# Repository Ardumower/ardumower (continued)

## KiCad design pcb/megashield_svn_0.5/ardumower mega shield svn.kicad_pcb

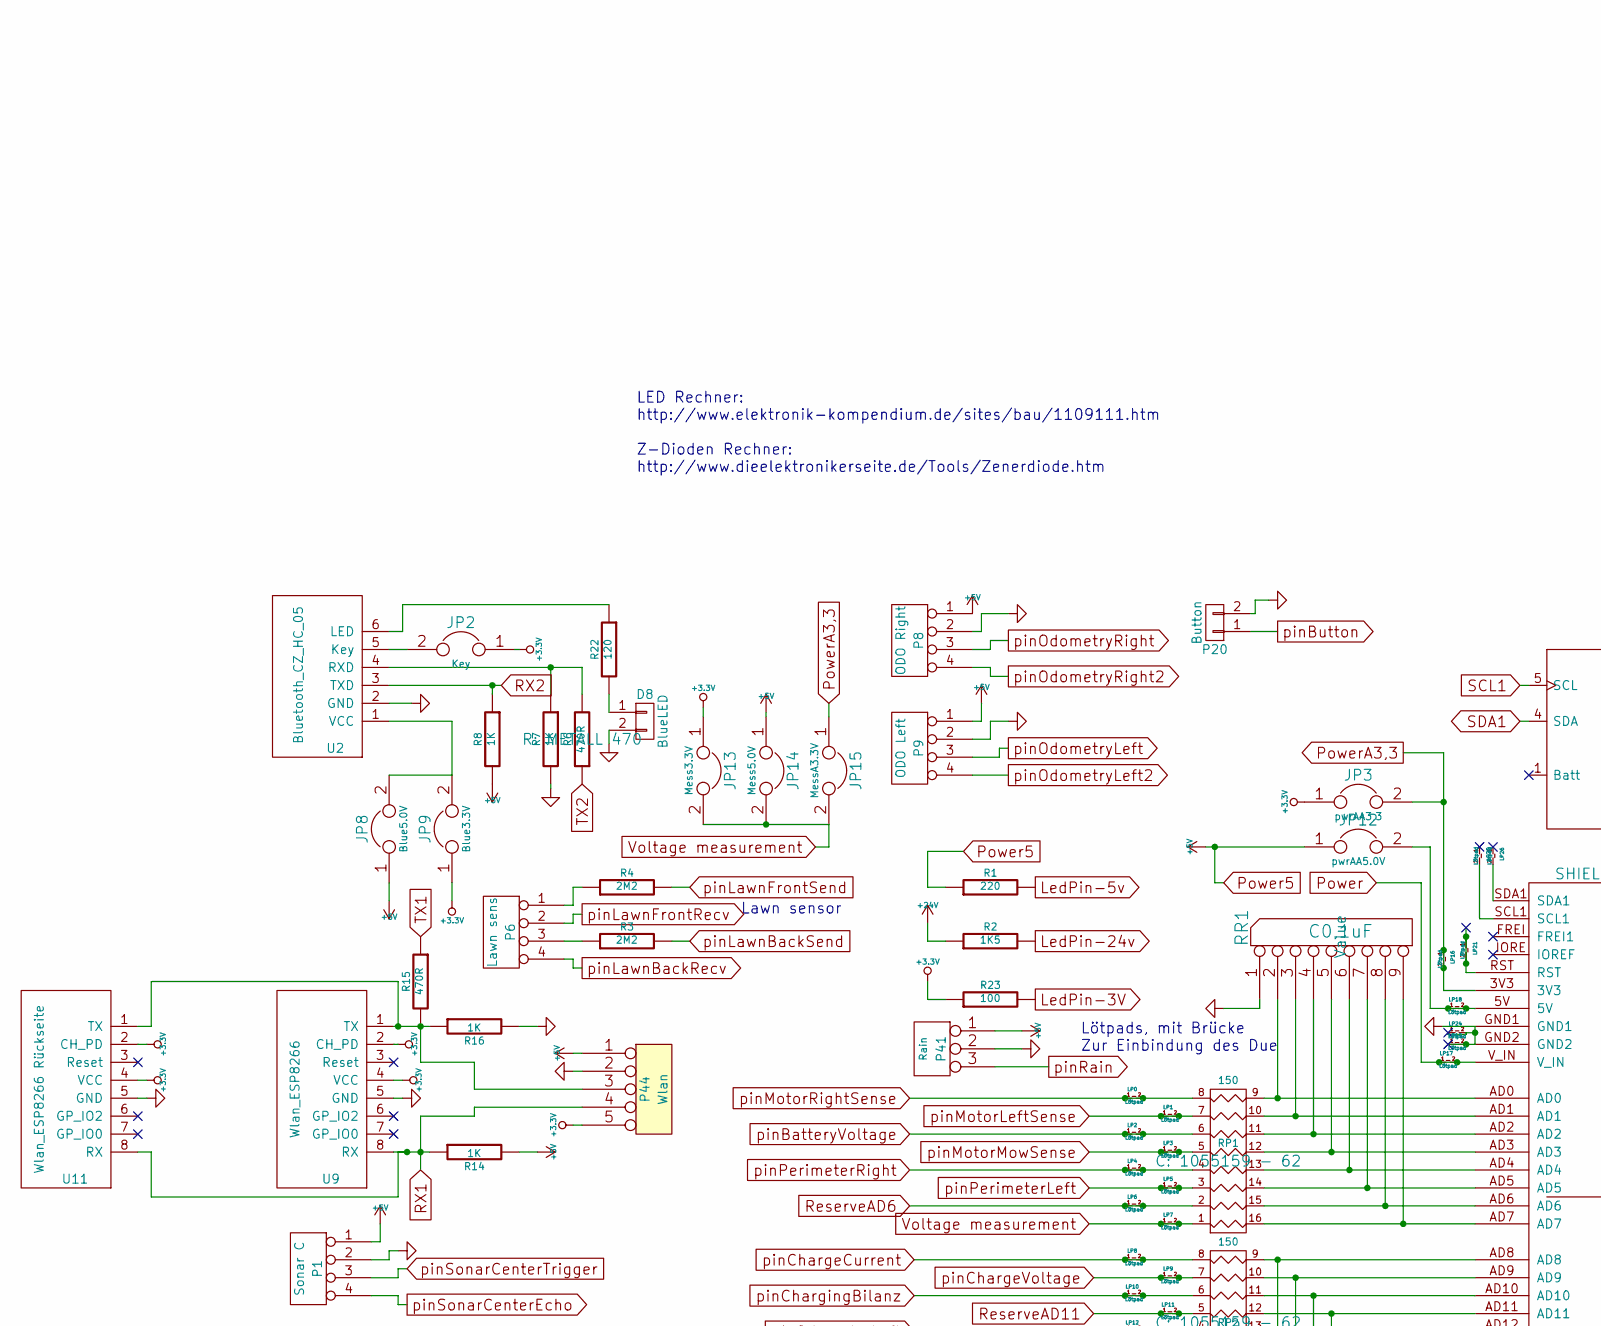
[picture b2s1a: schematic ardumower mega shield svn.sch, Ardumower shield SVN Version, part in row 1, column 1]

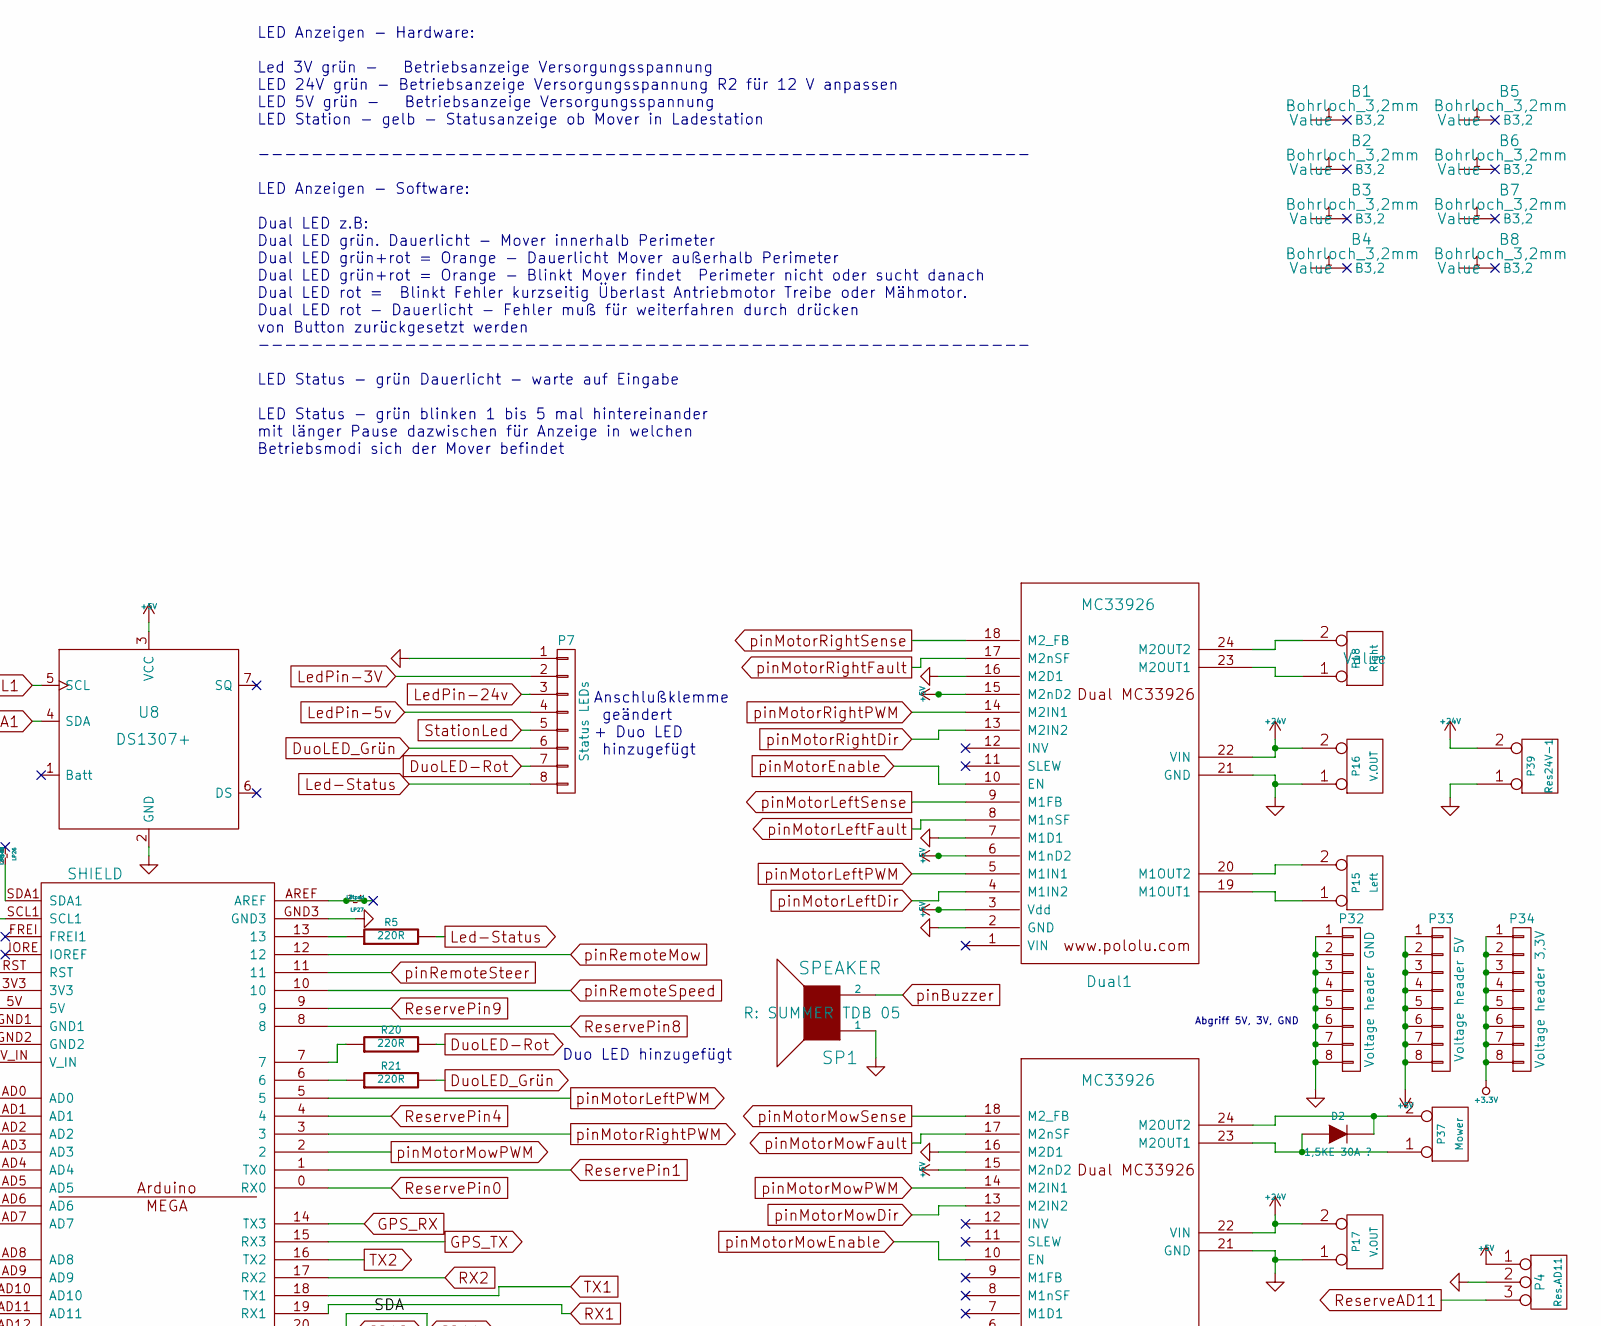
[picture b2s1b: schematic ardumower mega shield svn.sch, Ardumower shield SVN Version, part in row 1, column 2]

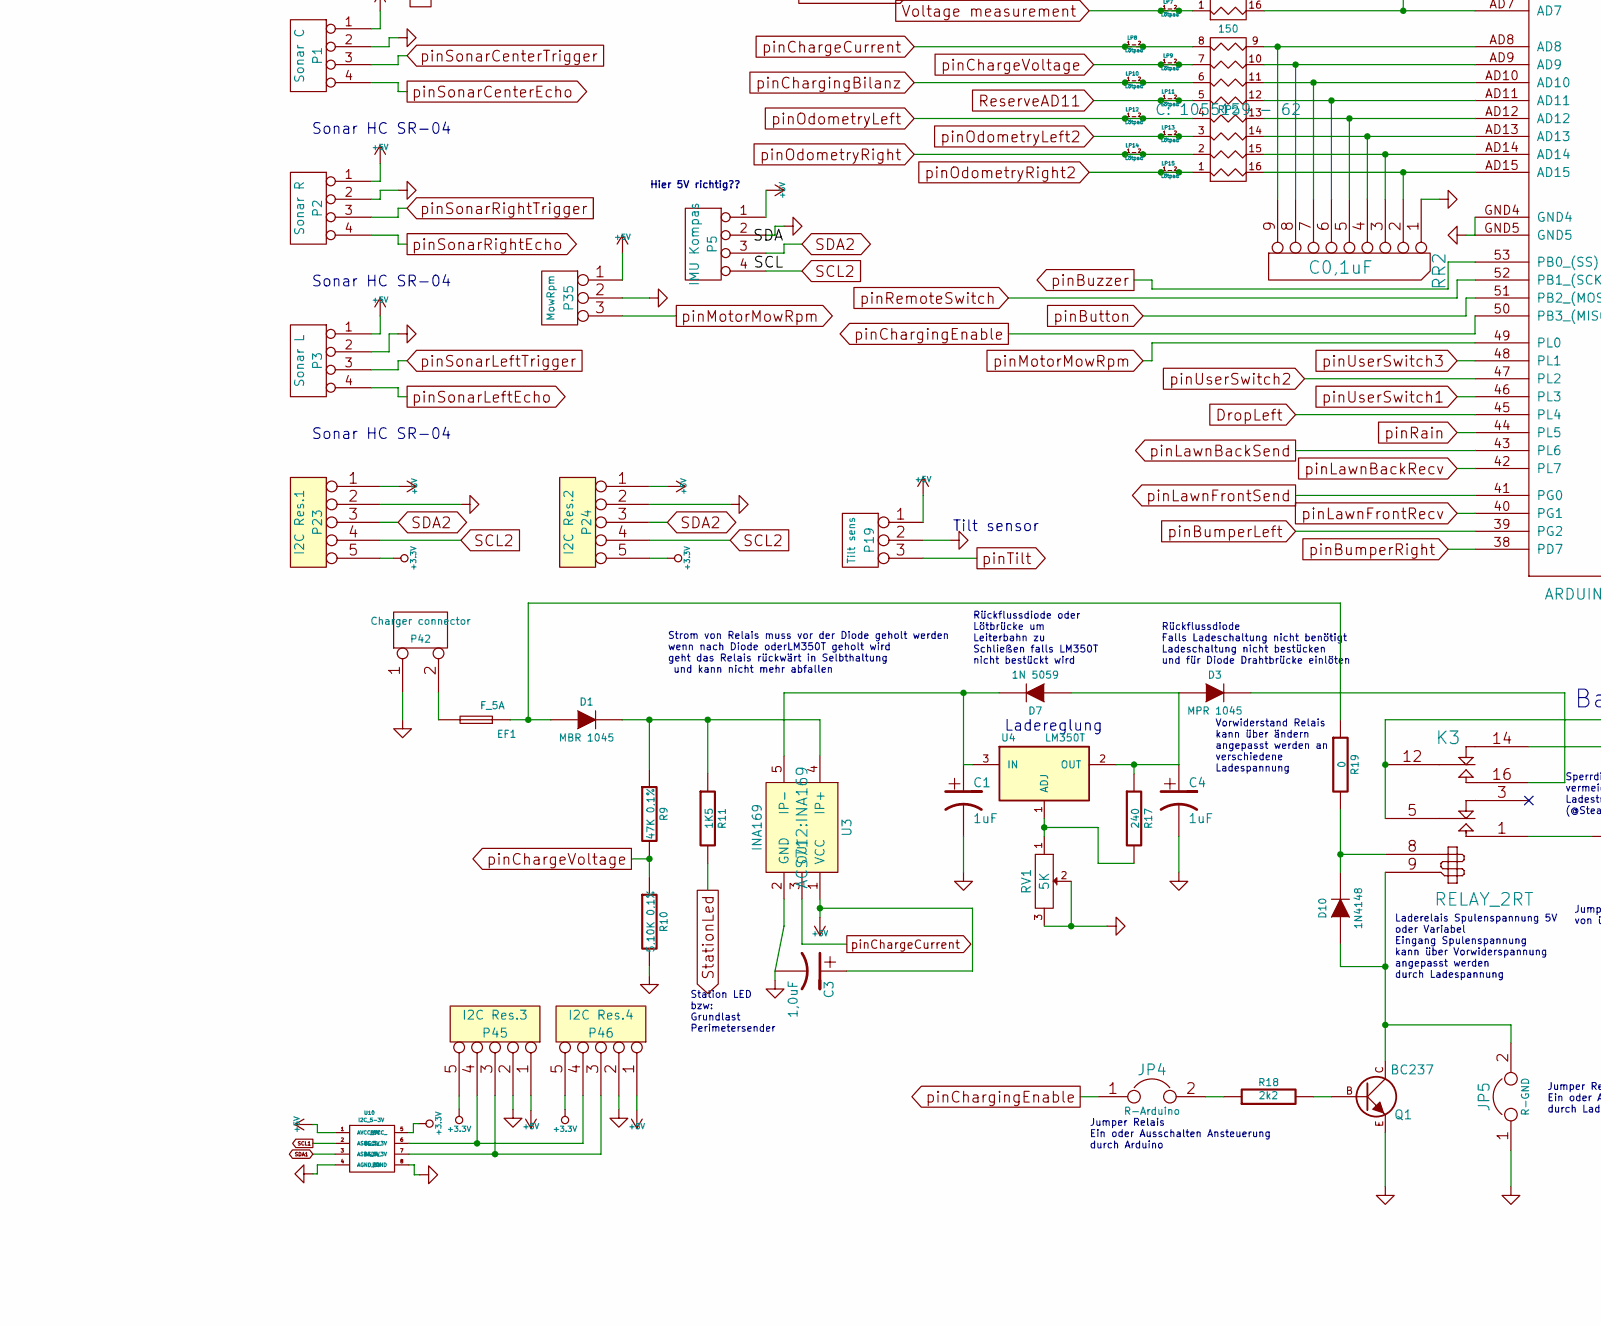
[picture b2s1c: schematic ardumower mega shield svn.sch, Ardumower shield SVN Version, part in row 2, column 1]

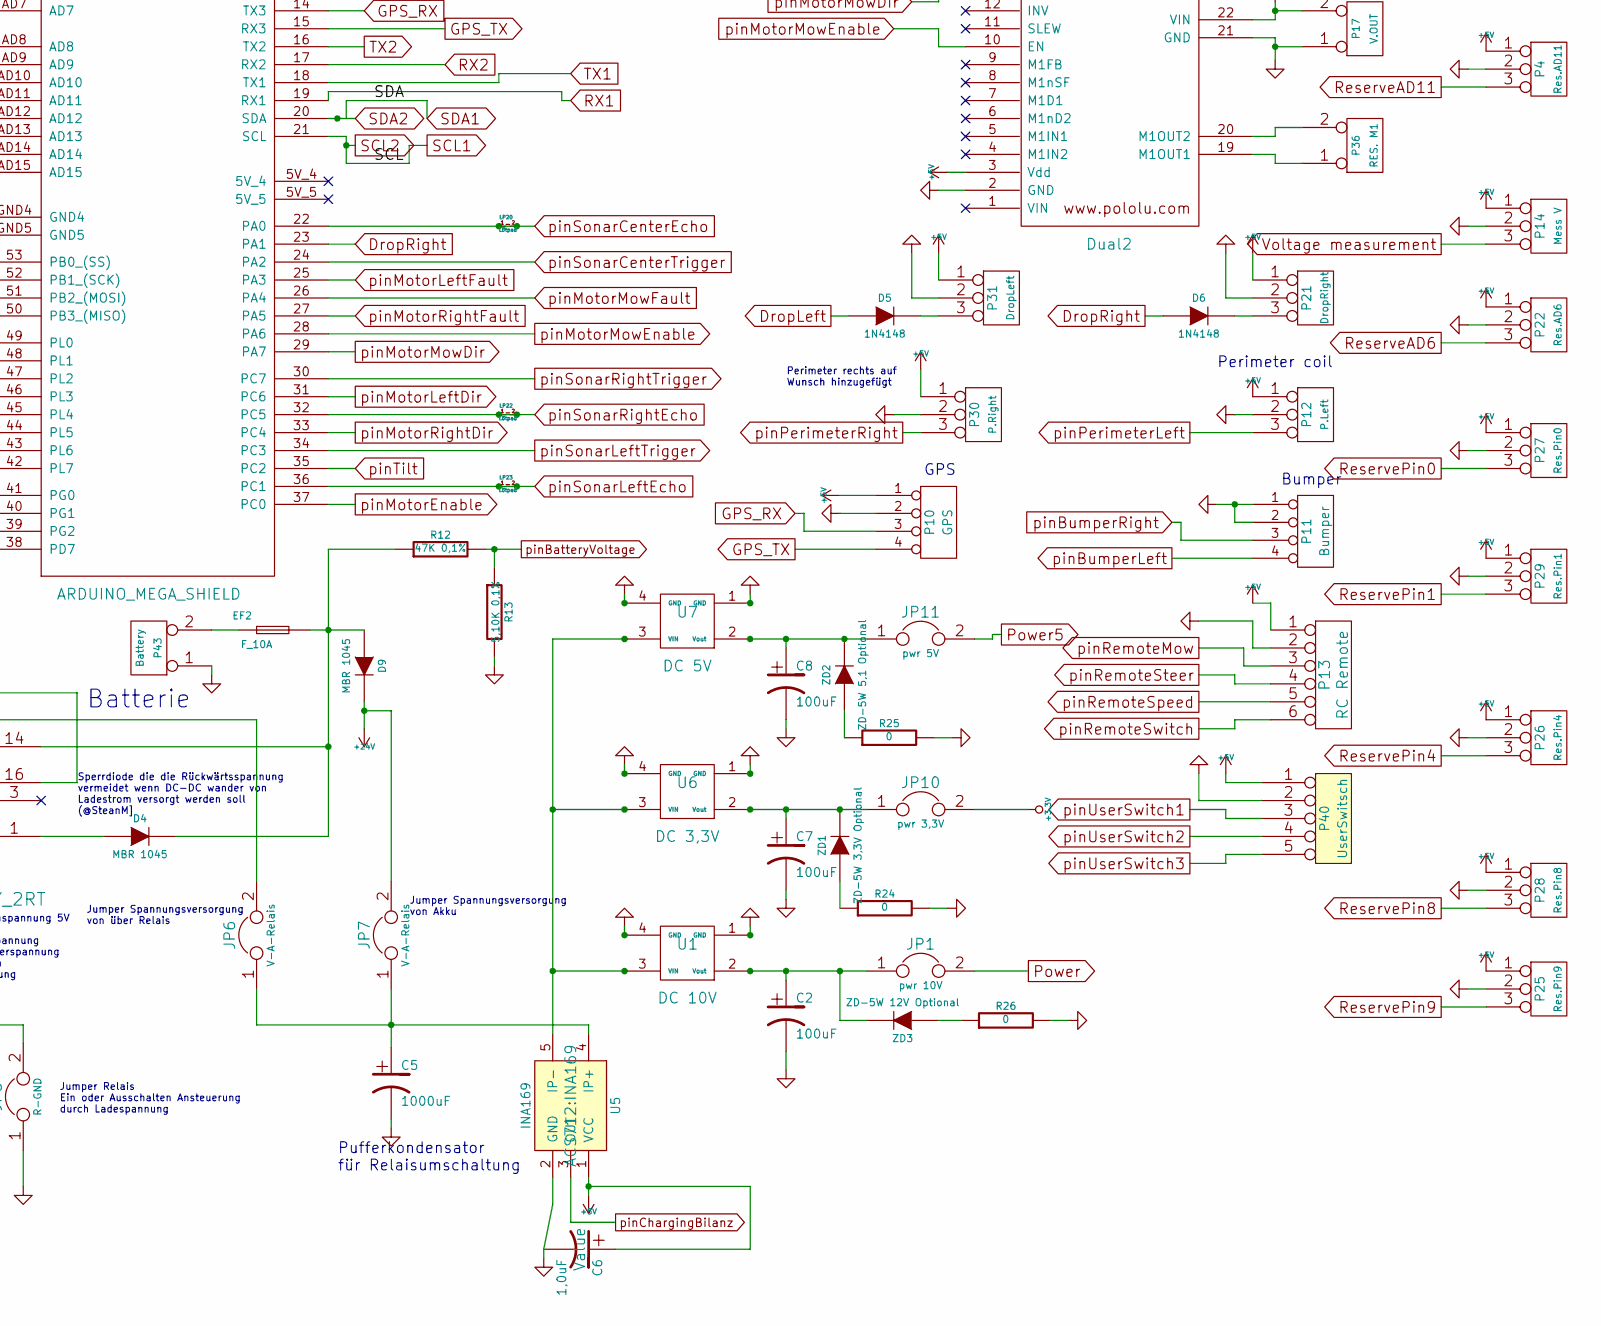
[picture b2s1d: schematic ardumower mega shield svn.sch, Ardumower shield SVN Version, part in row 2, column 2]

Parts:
B1, B2, B3, B4, B5, B6, B7, B8: Bohrloch_3,2mm
C1, C4: 1uF; Elko_vert_11.2x6.3mm_RM2.5_RM5.0
C2, C7, C8: 100uF; Elko_vert_11.2x6.3mm_RM2.5_RM5.0
C3, C6: 1,0uF; Elko_vert_11.2x6.3mm_RM2.5_RM5.0
C5: 1000uF; Elko_vert_31.5x16mm_RM7.5
D1, D4: MBR 1045; MBR1045
D2: 1,5KE 30A ?; Diode_ligend_RM10
D3: MPR 1045; MBR1045
D5, D6, D10: 1N4148; Diode_ligend_RM10
D7: 1N 5059; Diode_ligend_RM10
D8: BlueLED; Diode_LED_5mm_round_vertical
D9: MBR 1045; MBR1045_liegend
Dual1, Dual2: MC33926; MC_33926_31polig_mit_Bohrloch_neue_Masse
EF1: F_5A; Fuseholder_Reichelt_PL112000
EF2: F_10A; Fuseholder_Reichelt_PL112000
JP1: pwr 10V; Pin_Header_Straight_1x02
JP2: Key; Pin_Header_Straight_1x02
JP3: pwrAA3,3; Pin_Header_Straight_1x02
JP4: R-Arduino; Pin_Header_Straight_1x02
JP5: R-GND; Pin_Header_Straight_1x02
JP6, JP7: V-A-Relais; Pin_Header_Straight_1x02
JP8: Blue5.0V; Pin_Header_Straight_1x02
JP9: Blue3.3V; Pin_Header_Straight_1x02
JP10: pwr 3,3V; Pin_Header_Straight_1x02
JP11: pwr 5V; Pin_Header_Straight_1x02
JP12: pwrAA5.0V; Pin_Header_Straight_1x02
JP13: Mess3.3V; Pin_Header_Straight_1x02
JP14: Mess5.0V; Pin_Header_Straight_1x02
JP15: MessA3.3V; Pin_Header_Straight_1x02
K3: RELAY_2RT; Relais_DPDT_Schrack-RT2_RM5mm_3D_Kontaktbelegung_geändert_F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
LP0, LP1, LP2, LP3, LP4, LP5, LP6, LP7, LP8, LP9, LP10, LP11, LP12, LP13, LP14, LP15, LP16, LP17, LP18, LP19, LP20, LP21, LP22, LP23, LP24, LP25, LP26, LP27: Lötpad; Lötpad_1x02
P1: Sonar C; Pin_Header_Straight_1x04
P2: Sonar R; Pin_Header_Straight_1x04
P3: Sonar L; Pin_Header_Straight_1x04
P4: Res.AD11; Pin_Header_Straight_1x03
P5: IMU Kompas; Pin_Header_Straight_1x04
P6: Lawn sens; Pin_Header_Straight_1x04
P7: Status LEDs; Pin_Header_Straight_1x08
P8: ODO Right; Pin_Header_Straight_1x04
P9: ODO Left; Pin_Header_Straight_1x04
P10: GPS; Pin_Header_Straight_1x04
P11: Bumper; Pin_Header_Straight_1x04
P12: P.Left; Pin_Header_Straight_1x03
P13: RC Remote; Pin_Header_Straight_1x06
P14: Mess V; Pin_Header_Straight_1x03
P15: Left; Anschlussklemme_2P_RM5,08
P16, P17: V.OUT; Anschlussklemme_2P_RM5,08
P18: Right; Anschlussklemme_2P_RM5,08
P19: Tilt sens; Pin_Header_Straight_1x03
P20: Button; Pin_Header_Straight_1x02
P21: DropRight; Pin_Header_Straight_1x03
P22: Res.AD6; Pin_Header_Straight_1x03
P23: I2C Res.1; Pin_Header_Straight_1x05
P24: I2C Res.2; Pin_Header_Straight_1x05
P25: Res.Pin9; Pin_Header_Straight_1x03
P26: Res.Pin4; Pin_Header_Straight_1x03
P27: Res.Pin0; Pin_Header_Straight_1x03
P28: Res.Pin8; Pin_Header_Straight_1x03
P29: Res.Pin1; Pin_Header_Straight_1x03
P30: P.Right; Pin_Header_Straight_1x03
P31: DropLeft; Pin_Header_Straight_1x03
P32: Voltage header GND; Pin_Header_Straight_1x08
P33: Voltage header 5V; Pin_Header_Straight_1x08
P34: Voltage header 3,3V; Pin_Header_Straight_1x08
P35: MowRpm; Pin_Header_Straight_1x03
P36: RES. M1; Anschlussklemme_2P_RM5,08
P37: Mower; Anschlussklemme_2P_RM5,08
P39: Res24V-1; Anschlussklemme_2P_RM5,08
P40: UserSwitsch; Pin_Header_Straight_1x05
P41: Rain; Pin_Header_Straight_1x03
P42: Charger connector; Anschlussklemme_RM5,08-RM7,62
P43: Battery; Anschlussklemme_RM5,08-RM7,62
P44: Wlan; Pin_Header_Straight_1x05
P45: I2C Res.3; Pin_Header_Straight_1x05
P46: I2C Res.4; Pin_Header_Straight_1x05
Q1: BC237; TO92-EBC
R1: 220; Resistor_Horizontal_RM15mm
R2, R11: 1K5; Resistor_Horizontal_RM10mm
R3, R4: 2M2; Resistor_Horizontal_RM10mm
R5, R20, R21: 220R; Resistor_Horizontal_RM15mm
R6, R15: 470R; Resistor_Horizontal_RM15mm
R7, R8, R14, R16: 1K; Resistor_Horizontal_RM15mm
R9: 47K 0,1%; Resistor_Horizontal_RM10mm
R10: 5,10K 0,1%; Resistor_Horizontal_RM10mm
R12: 47K 0,1%; Resistor_Horizontal_RM15mm
R13: 5,10K 0,1%; Resistor_Horizontal_RM15mm
R17: 240; Resistor_Horizontal_RM15mm
R18: 2k2; Resistor_Horizontal_RM15mm
R19, R24, R25, R26: 0; Resistor_Horizontal_RM15mm
R22: 120; Resistor_Horizontal_RM15mm
R23: 100; Resistor_Horizontal_RM15mm
RP1, RP2: 150; DIP-16__300
RR1, RR2: C0,1uF; Kondensatorenleiste_8er_9pin_3D
RV1: 5K; Potentiometer_VishaySpectrol-Econtrim-Type36T_3D
SHIELD1: ARDUINO_MEGA_SHIELD; ARDUINO_MEGA_SHIELD_DUO_3D
SP1: SPEAKER; Buzzer_12x9.5RM7.6_RM5.0
U1: DC 10V; DC_DC_DSN2596_mit_Bohrloch
U2: Bluetooth_CZ_HC_05; Bluetooth_Buchse_Platz
U3, U5: INA169
U4: LM350T; LM350T_3D_muss_noch_auf_Masse_geprüft_werden
U6: DC 3,3V; DC_DC_DSN2596_mit_Bohrloch
U7: DC 5V; DC_DC_DSN2596_mit_Bohrloch
U8: DS1307+; Tiny_RTC_DS1307_geändert_mit_Bohrloch
U9: Wlan_ESP8266; Wlan_ESP8266_3D
U10: I2C_5-3V
U11: Wlan_ESP8266 Rückseite; Wlan_ESP8266_3D
ZD1: ZD-5W 3,3V Optional; Diode_ligend_RM10
ZD2: ZD-5W 5,1 Optional; Diode_ligend_RM10
ZD3: ZD-5W 12V Optional; Diode_ligend_RM10

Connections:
+3.3V: JP2.1, JP3.1, JP9.1, JP10.2, JP13.1, P23.5, P24.5, P34.1, P34.2, P34.3, P34.4, P34.5, P34.6, P34.7, P34.8, P44.5, P45.5, P46.5, R23.1, U9.2 (CH_PD), U9.4 (VCC), U10.5 (BVCC_), U11.2 (CH_PD), U11.4 (VCC)
+24V: D9.2 (K), Dual1.22 (VIN), Dual2.22 (VIN), JP7.2, P16.2 (PM), P17.2 (PM), P39.2 (PM), R2.1
DropLeft: D5.1 (A), SHIELD1.45 (PL4)
DropRight: D6.1 (A), SHIELD1.23 (PA1)
DuoLED-Rot: P7.7, R20.2
DuoLED_Grün: P7.6, R21.2
GND: C1.2, C2.2, C3.2, C4.2, C5.2, C6.2, C7.2, C8.2, D8.2, Dual1.2 (GND), Dual1.7 (M1D1), Dual1.16 (M2D1), Dual1.21 (GND), Dual2.2 (GND), Dual2.16 (M2D1), Dual2.21 (GND), JP5.1, LP19.1, LP19.2, LP24.1, LP24.2, P1.2, P2.2, P3.2, P4.2 (PM), P5.2, P7.1, P8.2, P9.2, P10.2, P11.1, P11.2, P12.2 (PM), P13.2, P14.2 (PM), P16.1, P17.1, P19.2 (PM), P20.2, P21.2 (PM), P22.2 (PM), P23.2, P24.2, P25.2 (PM), P26.2 (PM), P27.2 (PM), P28.2 (PM), P29.2 (PM), P30.2 (PM), P31.2 (PM), P32.1, P32.2, P32.3, P32.4, P32.5, P32.6, P32.7, P32.8, P35.2 (PM), P39.1, P40.2, P41.2 (PM), P42.1, P43.1, P44.2, P45.2, P46.2, Q1.E, R7.2, R10.2, R13.2, R16.2, R24.2, R25.2, R26.2, RR1.1 (COM), RR2.1 (COM), RV1.2, RV1.3, SHIELD1.GND1, SHIELD1.GND2, SHIELD1.GND3, SHIELD1.GND4, SHIELD1.GND5, SP1.1, U1.1 (GND), U1.4 (GND), U2.2 (GND), U3.2 (GND), U5.2 (GND), U6.1 (GND), U6.4 (GND), U7.1 (GND), U7.4 (GND), U8.2 (GND), U9.5 (GND), U10.4 (AGND_5V), U10.8 (BGND), U11.5 (GND)
GPS_RX: P10.3, SHIELD1.14 (TX3)
GPS_TX: P10.4, SHIELD1.15 (RX3)
Led-Status: P7.8, R5.2
LedPin-3V: P7.2, R23.2
LedPin-5v: P7.4, R1.2
LedPin-24v: P7.3, R2.2
unnamed: C1.1, D7.2 (K), U3.5 (IP-), U4.3 (IN)
unnamed: C2.1, JP1.1, U1.2 (Vout), ZD3.2 (K)
unnamed: C4.1, D3.1 (A), D7.1 (A), R17.1, U4.2 (OUT)
unnamed: C5.1, JP6.1, JP7.1, U5.4 (IP+)
unnamed: C7.1, JP10.1, U6.2 (Vout), ZD1.2 (K)
unnamed: C8.1, JP11.1, U7.2 (Vout), ZD2.2 (K)
unnamed: D1.1 (A), EF1.2, R19.1
unnamed: D1.2 (K), R9.1, R11.1, U3.4 (IP+)
unnamed: D2.1 (A), Dual2.23 (M2OUT1), P37.1
unnamed: D2.2 (K), Dual2.24 (M2OUT2), P37.2 (PM)
unnamed: D3.2 (K), K3.16 (T2)
unnamed: D4.1 (A), K3.1 (T1)
unnamed: D4.2 (K), D9.1 (A), EF2.1, K3.14 (R2), R12.1
unnamed: D5.2 (K), P31.3
unnamed: D6.2 (K), P21.3
unnamed: D8.1, R22.2
unnamed: D10.1 (A), JP5.2, K3.9, Q1.C
unnamed: D10.2 (K), K3.8, R19.2
unnamed: Dual1.19 (M1OUT1), P15.1
unnamed: Dual1.20 (M1OUT2), P15.2 (PM)
unnamed: Dual1.23 (M2OUT1), P18.1
unnamed: Dual1.24 (M2OUT2), P18.2 (PM)
unnamed: Dual2.19 (M1OUT1), P36.1
unnamed: Dual2.20 (M1OUT2), P36.2 (PM)
unnamed: EF1.1, P42.2 (PM)
unnamed: EF2.2, P43.2 (PM)
unnamed: JP2.2, U2.5 (Key)
unnamed: JP4.2, R18.1
unnamed: JP6.2, K3.5 (C1), K3.12 (C2)
unnamed: JP8.2, JP9.2, U2.1 (VCC)
unnamed: JP12.2, LP18.1, LP18.2, SHIELD1.5V
unnamed: LP21.1, LP21.2, SHIELD1.RST
unnamed: LP25.2, SHIELD1.SCL1
unnamed: LP26.2, SHIELD1.SDA1
unnamed: LP27.1, LP27.2, SHIELD1.AREF
unnamed: P6.1, R4.1
unnamed: P6.3, R3.1
unnamed: P44.3, R15.2, R16.1, U9.1 (TX), U11.1 (TX)
unnamed: P45.3, P46.3, U10.7 (BSDA_3V)
unnamed: P45.4, P46.4, U10.6 (BSCL_3V)
unnamed: Q1.B, R18.2
unnamed: R5.1, SHIELD1.13
unnamed: R6.2, R7.1, U2.4 (RXD)
unnamed: R17.2, RV1.1, U4.1 (ADJ)
unnamed: R20.1, SHIELD1.7
unnamed: R21.1, SHIELD1.6
unnamed: R22.1, U2.6 (LED)
unnamed: R24.1, ZD1.1 (A)
unnamed: R25.1, ZD2.1 (A)
unnamed: R26.1, ZD3.1 (A)
unnamed: RP1.9 (R8), RR1.2, SHIELD1.AD0
unnamed: RP1.10 (R7), RR1.3, SHIELD1.AD1
unnamed: RP1.11 (R6), RR1.4, SHIELD1.AD2
unnamed: RP1.12 (R5), RR1.5, SHIELD1.AD3
unnamed: RP1.13 (R4), RR1.6, SHIELD1.AD4
unnamed: RP1.14 (R3), RR1.7, SHIELD1.AD5
unnamed: RP1.15 (R2), RR1.8, SHIELD1.AD6
unnamed: RP1.16 (R1), RR1.9, SHIELD1.AD7
unnamed: RP2.9 (R8), RR2.9, SHIELD1.AD8
unnamed: RP2.10 (R7), RR2.8, SHIELD1.AD9
unnamed: RP2.11 (R6), RR2.7, SHIELD1.AD10
unnamed: RP2.12 (R5), RR2.6, SHIELD1.AD11
unnamed: RP2.13 (R4), RR2.5, SHIELD1.AD12
unnamed: RP2.14 (R3), RR2.4, SHIELD1.AD13
unnamed: RP2.15 (R2), RR2.3, SHIELD1.AD14
unnamed: RP2.16 (R1), RR2.2, SHIELD1.AD15
unnamed: U1.3 (VIN), U5.5 (IP-), U6.3 (VIN), U7.3 (VIN)
Power: JP1.2, LP17.1, LP17.2, SHIELD1.V_IN
Power5: C3.1, C6.1, Dual1.3 (Vdd), Dual1.6 (M1nD2), Dual1.15 (M2nD2), Dual2.3 (Vdd), Dual2.15 (M2nD2), JP8.1, JP11.2, JP12.1, JP14.1, P1.1, P2.1, P3.1, P4.1, P5.1, P8.1, P9.1, P10.1, P12.1, P13.1, P14.1, P19.1, P21.1, P22.1, P23.1, P24.1, P25.1, P26.1, P27.1, P28.1, P29.1, P30.1, P31.1, P33.1, P33.2, P33.3, P33.4, P33.5, P33.6, P33.7, P33.8, P35.1, P40.1, P41.1, P44.1, P45.1, P46.1, R1.1, R8.2, R14.2, U3.1 (VCC), U5.1 (VCC), U8.3 (VCC), U10.1 (AVCC_5V)
PowerA3,3: JP3.2, JP15.1, LP16.1, LP16.2, SHIELD1.3V3
RX1: P44.4, R14.1, SHIELD1.19 (RX1), U9.8 (RX), U11.8 (RX)
RX2: R8.1, SHIELD1.17 (RX2), U2.3 (TXD)
ReserveAD6: LP6.1, LP6.2, P22.3, RP1.2
ReserveAD11: LP11.1, LP11.2, P4.3, RP2.5
ReservePin0: P27.3, SHIELD1.0 (RX0)
ReservePin1: P29.3, SHIELD1.1 (TX0)
ReservePin4: P26.3, SHIELD1.4
ReservePin8: P28.3, SHIELD1.8
ReservePin9: P25.3, SHIELD1.9
SCL1: P5.4, P23.4, P24.4, SHIELD1.21 (SCL), U8.5 (SCL), U10.2 (ASCL_5V)
SDA2: P5.3, P23.3, P24.3, SHIELD1.20 (SDA), U8.4 (SDA), U10.3 (ASDA_5V)
StationLed: P7.5, R11.2
TX1: R15.1, SHIELD1.18 (TX1)
TX2: R6.1, SHIELD1.16 (TX2)
Voltage measurement: JP13.2, JP14.2, JP15.2, LP7.1, LP7.2, P14.3, RP1.1
pinBatteryVoltage: LP2.1, LP2.2, R12.2, R13.1, RP1.6
pinBumperLeft: P11.4, SHIELD1.39 (PG2)
pinBumperRight: P11.3, SHIELD1.38 (PD7)
pinButton: P20.1, SHIELD1.51 (PB2_(MOSI))
pinBuzzer: SHIELD1.53 (PB0_(SS)), SP1.2
pinChargeCurrent: LP8.1, LP8.2, RP2.8, U3.3 (OUT)
pinChargeVoltage: LP9.1, LP9.2, R9.2, R10.1, RP2.7
pinChargingBilanz: LP10.1, LP10.2, RP2.6, U5.3 (OUT)
pinChargingEnable: JP4.1, SHIELD1.50 (PB3_(MISO))
pinLawnBackRecv: P6.4, SHIELD1.42 (PL7)
pinLawnBackSend: R3.2, SHIELD1.43 (PL6)
pinLawnFrontRecv: P6.2, SHIELD1.40 (PG1)
pinLawnFrontSend: R4.2, SHIELD1.41 (PG0)
pinMotorEnable: Dual1.10 (EN), SHIELD1.37 (PC0)
pinMotorLeftDir: Dual1.4 (M1IN2), SHIELD1.31 (PC6)
pinMotorLeftFault: Dual1.8 (M1nSF), SHIELD1.25 (PA3)
pinMotorLeftPWM: Dual1.5 (M1IN1), SHIELD1.5
pinMotorLeftSense: Dual1.9 (M1FB), LP1.1, LP1.2, RP1.7
pinMotorMowDir: Dual2.13 (M2IN2), SHIELD1.29 (PA7)
pinMotorMowEnable: Dual2.10 (EN), SHIELD1.28 (PA6)
pinMotorMowFault: Dual2.17 (M2nSF), SHIELD1.26 (PA4)
pinMotorMowPWM: Dual2.14 (M2IN1), SHIELD1.2
pinMotorMowRpm: P35.3, SHIELD1.49 (PL0)
pinMotorMowSense: Dual2.18 (M2_FB), LP3.1, LP3.2, RP1.5
pinMotorRightDir: Dual1.13 (M2IN2), SHIELD1.33 (PC4)
pinMotorRightFault: Dual1.17 (M2nSF), SHIELD1.27 (PA5)
pinMotorRightPWM: Dual1.14 (M2IN1), SHIELD1.3
pinMotorRightSense: Dual1.18 (M2_FB), LP0.1, LP0.2, RP1.8
pinOdometryLeft: LP12.1, LP12.2, P9.3, RP2.4
pinOdometryLeft2: LP13.1, LP13.2, P9.4, RP2.3
pinOdometryRight: LP14.1, LP14.2, P8.3, RP2.2
pinOdometryRight2: LP15.1, LP15.2, P8.4, RP2.1
pinPerimeterLeft: LP5.1, LP5.2, P12.3, RP1.3
pinPerimeterRight: LP4.1, LP4.2, P30.3, RP1.4
pinRain: P41.3, SHIELD1.44 (PL5)
pinRemoteMow: P13.3, SHIELD1.12
pinRemoteSpeed: P13.5, SHIELD1.10
pinRemoteSteer: P13.4, SHIELD1.11
pinRemoteSwitch: P13.6, SHIELD1.52 (PB1_(SCK))
pinSonarCenterEcho: LP20.1, LP20.2, P1.4, SHIELD1.22 (PA0)
pinSonarCenterTrigger: P1.3, SHIELD1.24 (PA2)
pinSonarLeftEcho: LP23.1, LP23.2, P3.4, SHIELD1.36 (PC1)
pinSonarLeftTrigger: P3.3, SHIELD1.34 (PC3)
pinSonarRightEcho: LP22.1, LP22.2, P2.4, SHIELD1.32 (PC5)
pinSonarRightTrigger: P2.3, SHIELD1.30 (PC7)
pinTilt: P19.3, SHIELD1.35 (PC2)
pinUserSwitch1: P40.3, SHIELD1.46 (PL3)
pinUserSwitch2: P40.4, SHIELD1.47 (PL2)
pinUserSwitch3: P40.5, SHIELD1.48 (PL1)

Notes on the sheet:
Sonar HC SR-04
Perimeter coil
Lawn sensor
Tilt sensor
GPS
Bumper
Batterie
Pufferkondensator für Relaisumschaltung
Jumper Spannungsversorgung von Akku
Jumper Spannungsversorgung von über Relais
Jumper Relais Ein oder Ausschalten Ansteuerung durch Arduino
Jumper Relais Ein oder Ausschalten Ansteuerung durch Ladespannung
Laderelais Spulenspannung 5V oder Variabel Eingang Spulenspannung kann über Vorwiderspannung angepasst werden durch Ladespannung
Vorwiderstand Relais kann über ändern angepasst werden an verschiedene Ladespannung
Rückflussdiode Falls Ladeschaltung nicht benötigt Ladeschaltung nicht bestücken und für Diode Drahtbrücke einlöten
Anschlußklemme geändert + Duo LED hinzugefügt
Duo LED hinzugefügt
Station LED bzw: Grundlast Perimetersender
Strom von Relais muss vor der Diode geholt werden wenn nach Diode oderLM350T geholt wird geht das Relais rückwärt in Selbthaltung und kann nicht mehr abfallen
Hier 5V richtig??
Sperrdiode die die Rückwärtsspannung vermeidet wenn DC-DC wander von Ladestrom versorgt werden soll (@SteanM]
Rückflussdiode oder Lötbrücke um Leiterbahn zu Schließen falls LM350T nicht bestückt wird
Perimeter rechts auf Wunsch hinzugefügt
Abgriff 5V, 3V, GND
LED Anzeigen - Hardware: Led 3V grün - Betriebsanzeige Versorgungsspannung LED 24V grün - Betriebsanzeige Versorgungsspannung R2 für 12 V anpassen LED 5V grün - Betriebsanzeige Versorgungsspannung LED Station - gelb - Statusanzeige ob Mover in Ladestation -------------------------------------------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
LED Rechner: http://www.elektronik-kompendium.de/sites/bau/1109111.htm Z-Dioden Rechner: http://www.dieelektronikerseite.de/Tools/Zenerdiode.htm
Ladereglung
Lötpads, mit Brücke Zur Einbindung des Due

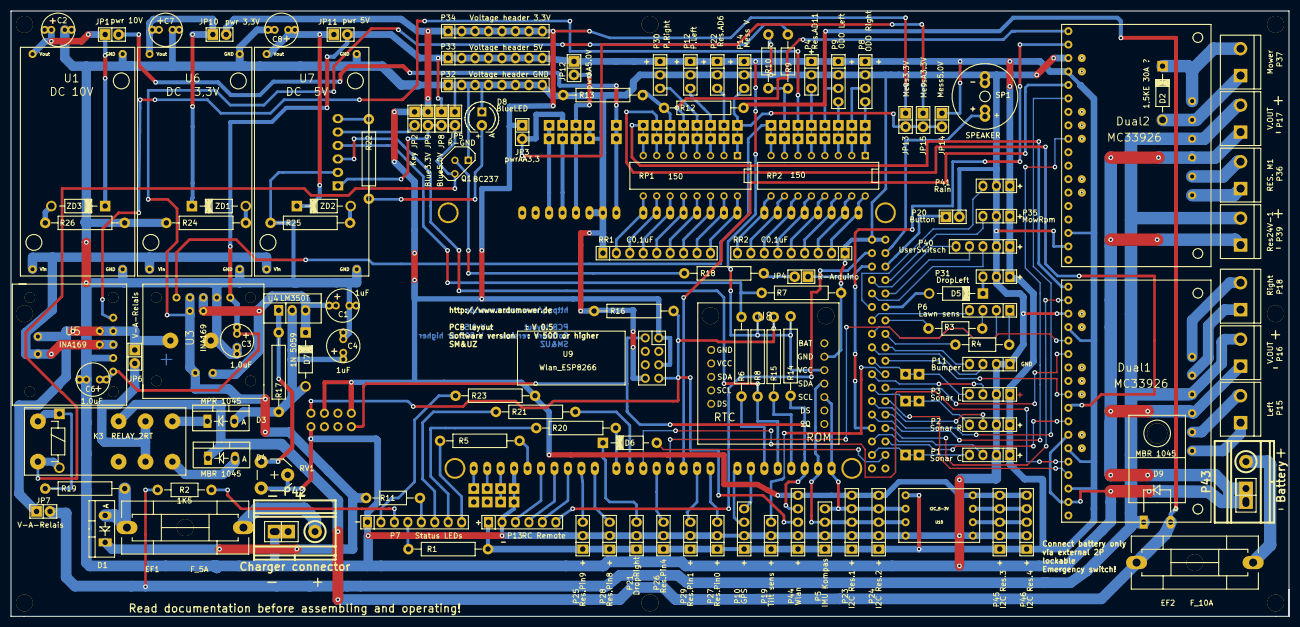
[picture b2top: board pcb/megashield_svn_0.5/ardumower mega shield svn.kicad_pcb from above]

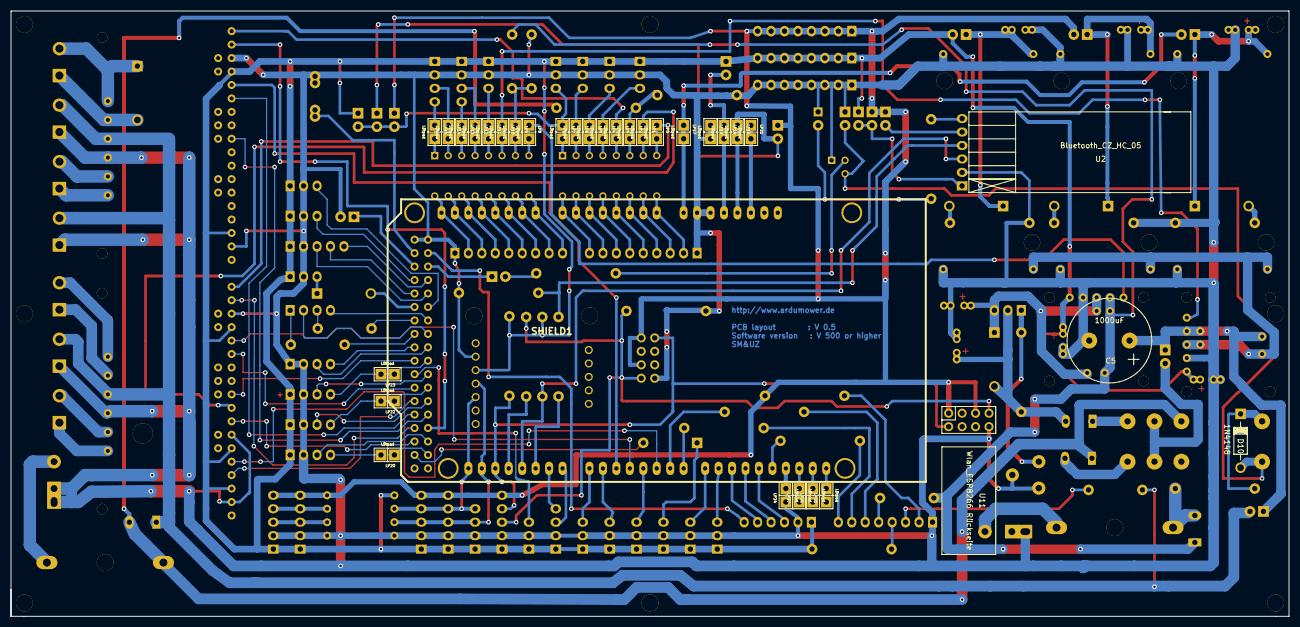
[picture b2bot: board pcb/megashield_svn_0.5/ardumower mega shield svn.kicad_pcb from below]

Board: 2 copper layers, 241.3 x 114.3 mm, 167 parts (33 on the bottom side), 147 nets.

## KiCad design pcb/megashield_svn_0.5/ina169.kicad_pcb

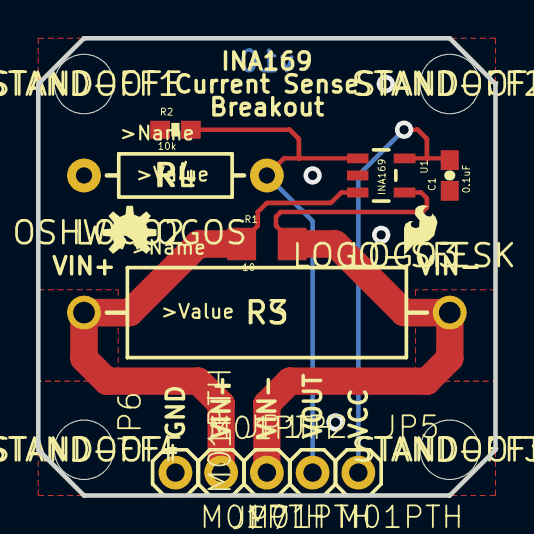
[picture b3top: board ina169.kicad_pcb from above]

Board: 2 copper layers, 25.4 x 25.4 mm, 19 parts (0 on the bottom side), 5 nets.

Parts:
C1: 0.1uF; 0603-CAP
FRAME1: FRAME-LETTER; CREATIVE_COMMONS
JP1, JP2, JP5, JP6, JP7: M01PTH; 1X01
LOGO1: SFE_LOGO_NAME_FLAME.1_INCH; SFE_LOGO_NAME_FLAME_.1
LOGO2: OSHW-LOGOS; OSHW-LOGO-S
LOGO3: LOGO-SFESK; SFE-LOGO-FLAME
R1: 10; 1206
R2: 10k; 0603-RES
R3: AXIAL-0.8
R4: AXIAL-0.4
STANDOFF1, STANDOFF2, STANDOFF3, STANDOFF4: STAND-OFF
U1: INA169; SOT23-5

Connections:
GND: C1.1, JP6.1, R2.1, R4.P$1, U1.2
VCC: C1.2, JP5.1, U1.5
VIN+: JP1.1, R1.1, R3.P$1, U1.3
VIN-: JP2.1, R1.2, R3.P$2, U1.4
VOUT: JP7.1, R2.2, R4.P$2, U1.1

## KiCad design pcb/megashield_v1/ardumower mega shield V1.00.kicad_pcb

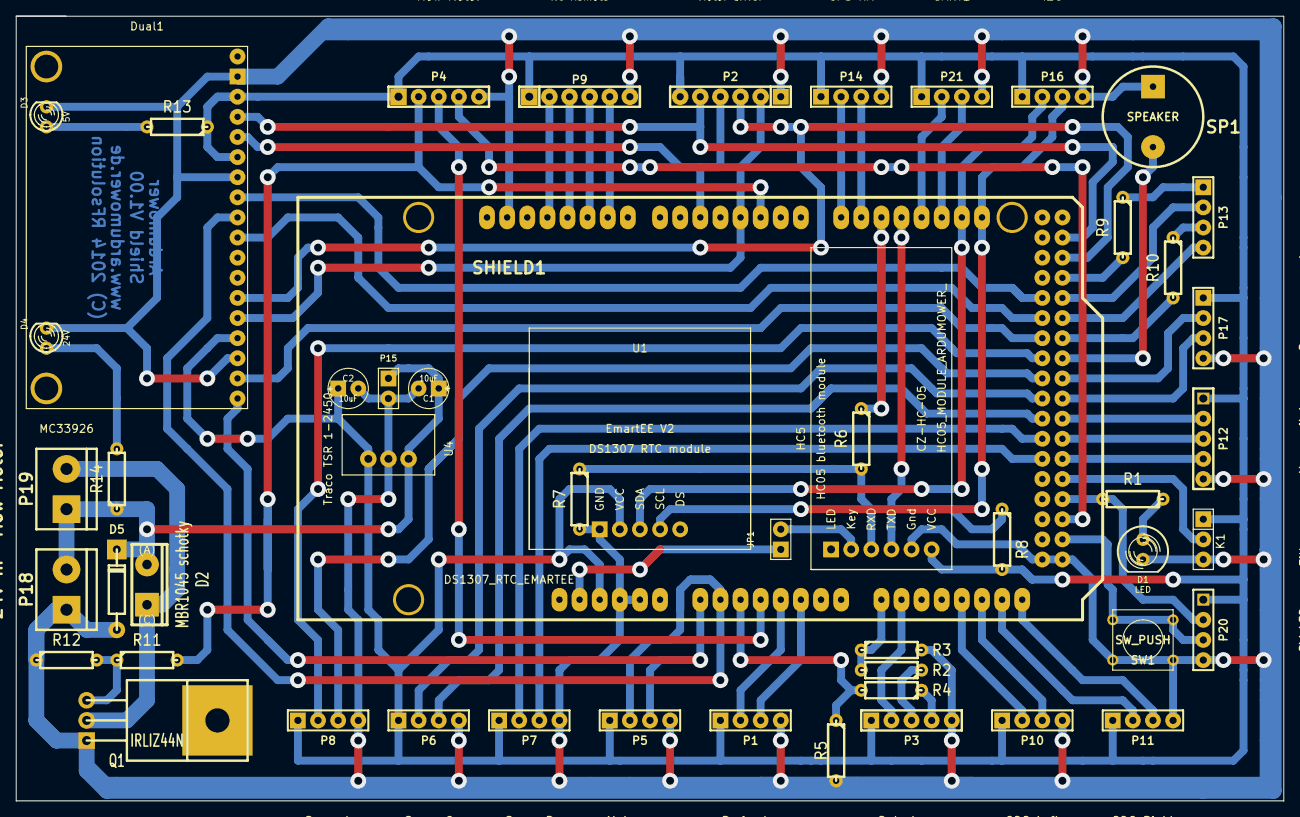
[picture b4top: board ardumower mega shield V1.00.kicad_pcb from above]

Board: 2 copper layers, 160.0 x 99.1 mm, 52 parts (0 on the bottom side), 67 nets.

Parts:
C1, C2: 10uF; C1V5
D1: LED; LED-5MM
D2: MBR1045 schotky; TO220_Diode_VERT
D3: 5V; LED-3MM
D4: 24V; LED-3MM
D5: 1N4007; DO-41
Dual1: MC33926; Dual_MC33926
HC5: HC05_MODULE_ARDUMOWER_; HC05_ardumowershop
JP1: JUMPER; PIN_ARRAY_2X1
K1: Tilt sens; PIN_ARRAY_3X1
P1: Perimeter; PIN_ARRAY_4x1
P2: Motor driver; PIN_ARRAY-6X1
P3: Bat charge; PIN_ARRAY_5x1
P4: Mow Motor; PIN_ARRAY_5x1
P5: Motor sens; PIN_ARRAY_4x1
P6: Sonar C; PIN_ARRAY_4x1
P7: Sonar R; PIN_ARRAY_4x1
P8: Sonar L; PIN_ARRAY_4x1
P9: RC Remote; PIN_ARRAY-6X1
P10: ODO Left; PIN_ARRAY_4x1
P11: ODO Right; PIN_ARRAY_4x1
P12: User switch; PIN_ARRAY_5x1
P13: Lawn sens; PIN_ARRAY_4x1
P14: GPS RX; PIN_ARRAY_4x1
P15: DC/DC; PIN_ARRAY_2X1
P16: I2C; PIN_ARRAY_4x1
P17: Bumper; PIN_ARRAY_4x1
P18: 24V in; bornier2
P19: Mow Motor; bornier2
P20: SW_LED; PIN_ARRAY_4x1
P21: UART1; PIN_ARRAY_4x1
Q1: IRLIZ44N; TO220GDS
R1, R6: 470R; R3-LARGE_PADS
R2, R4: 47K; R3-LARGE_PADS
R3, R5: 5K; R3-LARGE_PADS
R7, R8: 1K; R3-LARGE_PADS
R9, R10: 2M2; R3-LARGE_PADS
R11: 180; R3-LARGE_PADS
R12: 10K; R3-LARGE_PADS
R13: 470r; R3-LARGE_PADS
R14: 2k2; R3-LARGE_PADS
SHIELD1: ARDUINO_MEGA_SHIELD; ARDUINO MEGA SHIELD
SP1: SPEAKER; BUZ3-5
SW1: SW_PUSH; SW_PUSH_SMALL
U1: DS1307_RTC_EMARTEE; DS1307_Tiny_EmartEE
U4: Traco TSR 1-2450; Traco_TSR1_DCDC

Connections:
+3.3V: JP1.1, SHIELD1.3V3
+5V: C2.1, Dual1.3, Dual1.6, Dual1.15, HC5.6, K1.1, P1.1, P2.6, P3.1, P4.1, P5.1, P6.1, P7.1, P8.1, P9.1, P10.1, P11.1, P12.1, P14.1, P16.1, P17.1, P20.1, P21.1, R8.2, R13.1, SHIELD1.5V, U1.2, U4.VO
+24V: C1.1, D2.2, D5.2, P15.1, P18.2, P19.1, R14.1, U4.VI
BatteryVoltage: R4.2, R5.1, SHIELD1.AD2
BumperLeft: P17.3, SHIELD1.39
BumperRight: P17.2, SHIELD1.37
Button: P20.3, SHIELD1.53, SW1.2
Buzzer: SHIELD1.35, SP1.2
ChargeCurrent: P3.2, SHIELD1.AD9
ChargeVoltage: R2.2, R3.1, SHIELD1.AD8
GND: C1.2, C2.2, D1.2, D3.2, D4.2, D5.1, Dual1.2, Dual1.7, Dual1.16, HC5.5, K1.3, P1.4, P2.1, P3.5, P4.5, P5.4, P6.4, P7.4, P8.4, P9.6, P10.4, P11.4, P12.5, P14.4, P15.2, P16.4, P17.4, P18.1, P20.4, P21.4, Q1.S, R3.2, R5.2, R7.2, R12.1, SHIELD1.GND1, SHIELD1.GND2, SHIELD1.GND3, SHIELD1.GND4, SHIELD1.GND5, SP1.1, SW1.1, U1.1, U4.GND
GPS_RX: P14.2, SHIELD1.14
GPS_TX: P14.3, SHIELD1.15
LawnBackRecv: P13.2, SHIELD1.29
LawnBackSend: R9.2, SHIELD1.27
LawnFrontRecv: P13.4, SHIELD1.31
LawnFrontSend: R10.2, SHIELD1.33
Led: P20.2, R1.2, SHIELD1.49
Left perimeter: P1.3, SHIELD1.AD5
MotorEnable: Dual1.10, SHIELD1.30
MotorLeftDir: Dual1.4, P2.5, SHIELD1.23
MotorLeftFault: Dual1.8, SHIELD1.28
MotorLeftPWM: Dual1.5, P2.4, SHIELD1.5
MotorLeftSense: Dual1.9, P5.2, SHIELD1.AD1
MotorMow: P4.2, R11.2, SHIELD1.2
MotorMowRpm: P4.4, SHIELD1.51
MotorMowSense: P4.3, SHIELD1.AD3
MotorRightDir: Dual1.13, P2.3, SHIELD1.25
MotorRightFault: Dual1.17, SHIELD1.32
MotorRightPWM: Dual1.14, P2.2, SHIELD1.3
MotorRightSense: Dual1.18, P5.3, SHIELD1.AD0
unnamed: P13.1, R9.1
unnamed: P13.3, R10.1
unnamed: Q1.G, R11.1, R12.2
unnamed: HC5.2, JP1.2
unnamed: D2.1, P19.2, Q1.D
unnamed: D3.1, R13.2
unnamed: D4.1, R14.2
unnamed: D1.1, R1.1
unnamed: P3.4, R4.1
unnamed: HC5.3, R6.2, R7.1
unnamed: P3.3, R2.1
OdometryLeft: P10.2, SHIELD1.AD12
OdometryLeft2: P10.3, SHIELD1.AD13
OdometryRight: P11.2, SHIELD1.AD14
OdometryRight2: P11.3, SHIELD1.AD15
RX1: P21.3, SHIELD1.19
RX2: HC5.4, R8.1, SHIELD1.17
RemoteMow: P9.2, SHIELD1.12
RemoteSpeed: P9.4, SHIELD1.10
RemoteSteer: P9.3, SHIELD1.11
RemoteSwitch: P9.5, SHIELD1.9
Right perimeter: P1.2, SHIELD1.AD4
SCL: P16.3, SHIELD1.21, U1.4
SDA: P16.2, SHIELD1.20, U1.3
SonarCenterEcho: P6.3, SHIELD1.40
SonarCenterTrigger: P6.2, SHIELD1.38
SonarLeftEcho: P8.3, SHIELD1.36
SonarLeftTrigger: P8.2, SHIELD1.34
SonarRightEcho: P7.3, SHIELD1.44
SonarRightTrigger: P7.2, SHIELD1.42
TX1: P21.2, SHIELD1.18
TX2: R6.1, SHIELD1.16
Tilt: K1.2, SHIELD1.47
UserSwitch1: P12.2, SHIELD1.41
UserSwitch2: P12.3, SHIELD1.43
UserSwitch3: P12.4, SHIELD1.45
